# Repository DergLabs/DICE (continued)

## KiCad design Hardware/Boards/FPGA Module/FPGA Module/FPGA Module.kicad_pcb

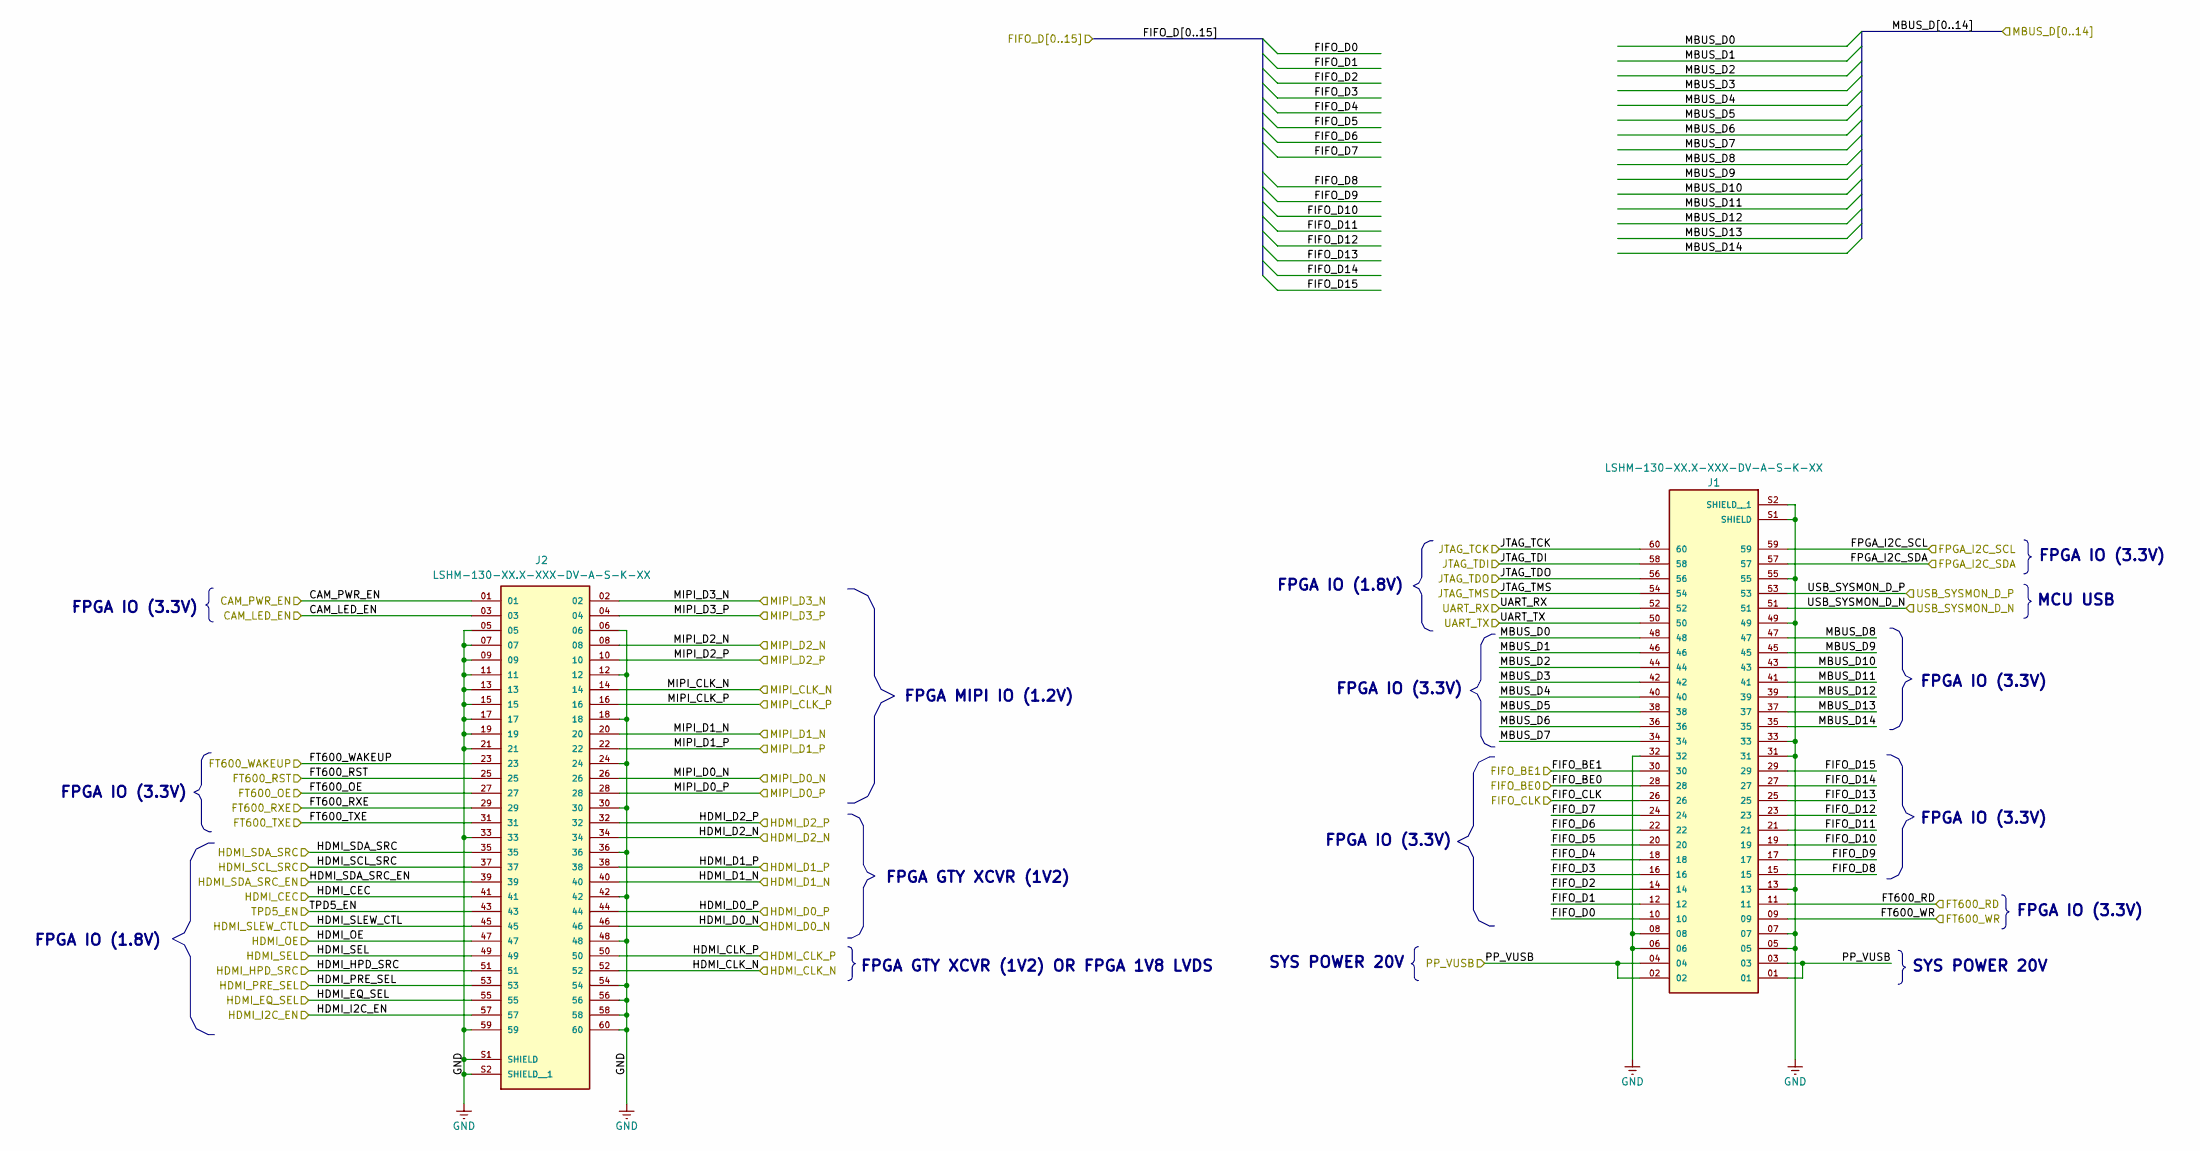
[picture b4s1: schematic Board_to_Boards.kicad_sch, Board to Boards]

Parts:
J1, J2: LSHM-130-XX.X-XXX-DV-A-S-K-XX; SAMTEC_LSHM-130-XX.X-XXX-DV-A-S-K-XX; PARTREV G

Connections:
/Top/Board to Boards/CAM_LED_EN: J2.03; also elsewhere on the board
/Top/Board to Boards/CAM_PWR_EN: J2.01; also elsewhere on the board
/Top/Board to Boards/FIFO_BE0: J1.28; also elsewhere on the board
/Top/Board to Boards/FIFO_BE1: J1.30; also elsewhere on the board
/Top/Board to Boards/FIFO_CLK: J1.26; also elsewhere on the board
/Top/Board to Boards/FIFO_D0: J1.10; also elsewhere on the board
/Top/Board to Boards/FIFO_D1: J1.12; also elsewhere on the board
/Top/Board to Boards/FIFO_D2: J1.14; also elsewhere on the board
/Top/Board to Boards/FIFO_D3: J1.16; also elsewhere on the board
/Top/Board to Boards/FIFO_D4: J1.18; also elsewhere on the board
/Top/Board to Boards/FIFO_D5: J1.20; also elsewhere on the board
/Top/Board to Boards/FIFO_D6: J1.22; also elsewhere on the board
/Top/Board to Boards/FIFO_D7: J1.24; also elsewhere on the board
/Top/Board to Boards/FIFO_D8: J1.15; also elsewhere on the board
/Top/Board to Boards/FIFO_D9: J1.17; also elsewhere on the board
/Top/Board to Boards/FIFO_D10: J1.19; also elsewhere on the board
/Top/Board to Boards/FIFO_D11: J1.21; also elsewhere on the board
/Top/Board to Boards/FIFO_D12: J1.23; also elsewhere on the board
/Top/Board to Boards/FIFO_D13: J1.25; also elsewhere on the board
/Top/Board to Boards/FIFO_D14: J1.27; also elsewhere on the board
/Top/Board to Boards/FIFO_D15: J1.29; also elsewhere on the board
/Top/Board to Boards/FPGA_I2C_SCL: J1.59; also elsewhere on the board
/Top/Board to Boards/FPGA_I2C_SDA: J1.57; also elsewhere on the board
/Top/Board to Boards/FT600_OE: J2.27; also elsewhere on the board
/Top/Board to Boards/FT600_RD: J1.11; also elsewhere on the board
/Top/Board to Boards/FT600_RST: J2.25; also elsewhere on the board
/Top/Board to Boards/FT600_RXE: J2.29; also elsewhere on the board
/Top/Board to Boards/FT600_TXE: J2.31; also elsewhere on the board
/Top/Board to Boards/FT600_WAKEUP: J2.23; also elsewhere on the board
/Top/Board to Boards/FT600_WR: J1.09; also elsewhere on the board
/Top/Board to Boards/HDMI_CEC: J2.41; also elsewhere on the board
/Top/Board to Boards/HDMI_CLK_N: J2.52; also elsewhere on the board
/Top/Board to Boards/HDMI_CLK_P: J2.50; also elsewhere on the board
/Top/Board to Boards/HDMI_D0_N: J2.46; also elsewhere on the board
/Top/Board to Boards/HDMI_D0_P: J2.44; also elsewhere on the board
/Top/Board to Boards/HDMI_D1_N: J2.40; also elsewhere on the board
/Top/Board to Boards/HDMI_D1_P: J2.38; also elsewhere on the board
/Top/Board to Boards/HDMI_D2_N: J2.34; also elsewhere on the board
/Top/Board to Boards/HDMI_D2_P: J2.32; also elsewhere on the board
/Top/Board to Boards/HDMI_EQ_SEL: J2.55; also elsewhere on the board
/Top/Board to Boards/HDMI_HPD_SRC: J2.51; also elsewhere on the board
/Top/Board to Boards/HDMI_I2C_EN: J2.57; also elsewhere on the board
/Top/Board to Boards/HDMI_OE: J2.47; also elsewhere on the board
/Top/Board to Boards/HDMI_PRE_SEL: J2.53; also elsewhere on the board
/Top/Board to Boards/HDMI_SCL_SRC: J2.37; also elsewhere on the board
/Top/Board to Boards/HDMI_SDA_SRC: J2.35; also elsewhere on the board
/Top/Board to Boards/HDMI_SDA_SRC_EN: J2.39; also elsewhere on the board
/Top/Board to Boards/HDMI_SEL: J2.49; also elsewhere on the board
/Top/Board to Boards/HDMI_SLEW_CTL: J2.45; also elsewhere on the board
/Top/Board to Boards/JTAG_TCK: J1.60; also elsewhere on the board
/Top/Board to Boards/JTAG_TDI: J1.58; also elsewhere on the board
/Top/Board to Boards/JTAG_TDO: J1.56; also elsewhere on the board
/Top/Board to Boards/JTAG_TMS: J1.54; also elsewhere on the board
/Top/Board to Boards/MBUS_D0: J1.48; also elsewhere on the board
/Top/Board to Boards/MBUS_D1: J1.46; also elsewhere on the board
/Top/Board to Boards/MBUS_D2: J1.44; also elsewhere on the board
/Top/Board to Boards/MBUS_D3: J1.42; also elsewhere on the board
/Top/Board to Boards/MBUS_D4: J1.40; also elsewhere on the board
/Top/Board to Boards/MBUS_D5: J1.38; also elsewhere on the board
/Top/Board to Boards/MBUS_D6: J1.36; also elsewhere on the board
/Top/Board to Boards/MBUS_D7: J1.34; also elsewhere on the board
/Top/Board to Boards/MBUS_D8: J1.47; also elsewhere on the board
/Top/Board to Boards/MBUS_D9: J1.45; also elsewhere on the board
/Top/Board to Boards/MBUS_D10: J1.43; also elsewhere on the board
/Top/Board to Boards/MBUS_D11: J1.41; also elsewhere on the board
/Top/Board to Boards/MBUS_D12: J1.39; also elsewhere on the board
/Top/Board to Boards/MBUS_D13: J1.37; also elsewhere on the board
/Top/Board to Boards/MBUS_D14: J1.35; also elsewhere on the board
/Top/Board to Boards/MIPI_CLK_N: J2.14; also elsewhere on the board
/Top/Board to Boards/MIPI_CLK_P: J2.16; also elsewhere on the board
/Top/Board to Boards/MIPI_D0_N: J2.26; also elsewhere on the board
/Top/Board to Boards/MIPI_D0_P: J2.28; also elsewhere on the board
/Top/Board to Boards/MIPI_D1_N: J2.20; also elsewhere on the board
/Top/Board to Boards/MIPI_D1_P: J2.22; also elsewhere on the board
/Top/Board to Boards/MIPI_D2_N: J2.08; also elsewhere on the board
/Top/Board to Boards/MIPI_D2_P: J2.10; also elsewhere on the board
/Top/Board to Boards/MIPI_D3_N: J2.02; also elsewhere on the board
/Top/Board to Boards/MIPI_D3_P: J2.04; also elsewhere on the board
/Top/Board to Boards/PP_VUSB: J1.01, J1.02, J1.03, J1.04; also elsewhere on the board
/Top/Board to Boards/TPD5_EN: J2.43; also elsewhere on the board
/Top/Board to Boards/UART_RX: J1.52; also elsewhere on the board
/Top/Board to Boards/UART_TX: J1.50; also elsewhere on the board
/Top/Board to Boards/USB_SYSMON_D_N: J1.51; also elsewhere on the board
/Top/Board to Boards/USB_SYSMON_D_P: J1.53; also elsewhere on the board

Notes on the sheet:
FPGA IO (3.3V)
FPGA GTY XCVR (1V2) OR FPGA 1V8 LVDS
FPGA GTY XCVR (1V2)
SYS POWER 20V
FPGA MIPI IO (1.2V)
MCU USB
FPGA IO (1.8V)

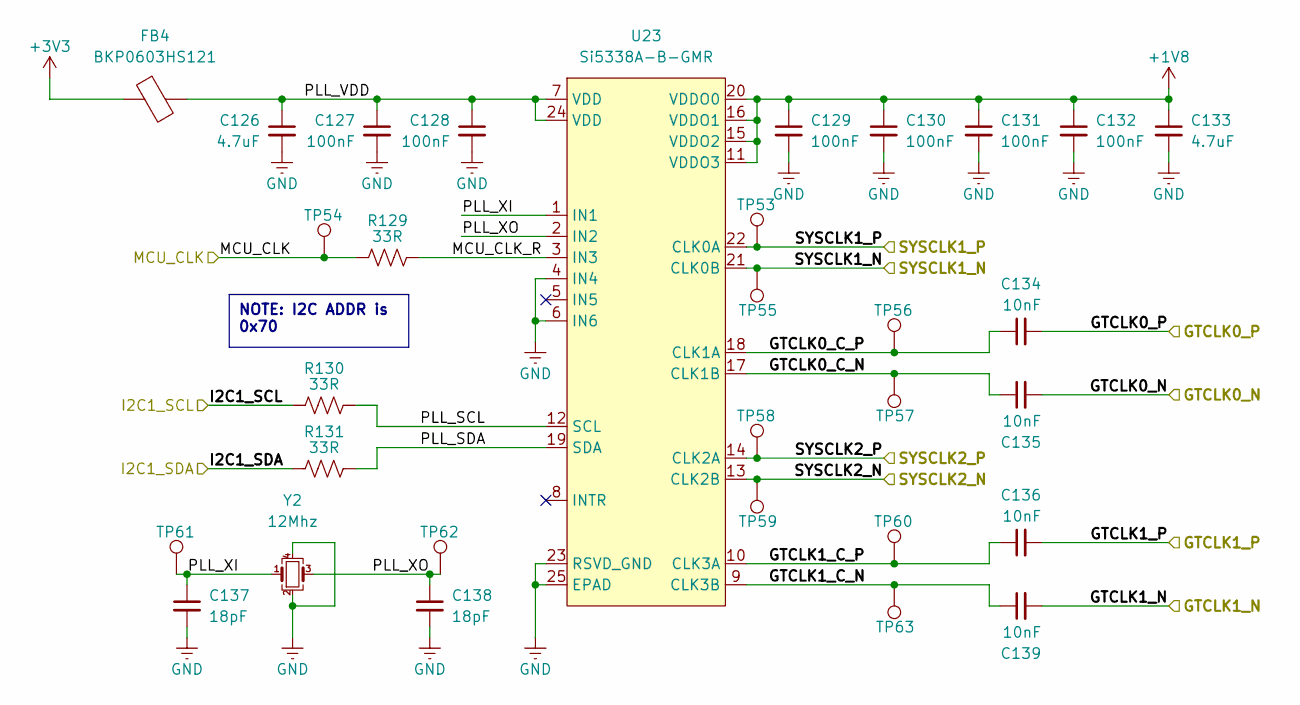
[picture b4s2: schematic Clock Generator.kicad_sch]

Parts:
C126, C133: 4.7uF; C_0402_1005Metric
C127, C128, C129, C130, C131, C132: 100nF; C_0201_0603Metric
C134, C135, C136, C139: 10nF; C_0201_0603Metric
C137, C138: 18pF; C_0201_0603Metric
FB4: BKP0603HS121; L_0201_0603Metric
R129, R130, R131: 33R; R_0201_0603Metric
TP53, TP54, TP55, TP56, TP57, TP58, TP59, TP60, TP61, TP62, TP63: Test Point; Test Point 0.75mm
U23: Si5338A-B-GMR; QFN-24-1EP_4x4mm_P0.5mm_EP2.6x2.6mm
Y2: 12Mhz; Oscillator_SMD_Abracon_ASE-4Pin_3.2x2.5mm

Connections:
+1V8: C129.1, C130.1, C131.1, C132.1, C133.1, U23.11 (VDDO3), U23.15 (VDDO2), U23.16 (VDDO1), U23.20 (VDDO0); also elsewhere on the board
/Top/Clock Generator/GTCLK0_C_N: C135.1, TP57.1, U23.17 (CLK1B)
/Top/Clock Generator/GTCLK0_C_P: C134.1, TP56.1, U23.18 (CLK1A)
/Top/Clock Generator/GTCLK0_N: C135.2; also elsewhere on the board
/Top/Clock Generator/GTCLK0_P: C134.2; also elsewhere on the board
/Top/Clock Generator/GTCLK1_C_N: C139.1, TP63.1, U23.9 (CLK3B)
/Top/Clock Generator/GTCLK1_C_P: C136.1, TP60.1, U23.10 (CLK3A)
/Top/Clock Generator/GTCLK1_N: C139.2; also elsewhere on the board
/Top/Clock Generator/GTCLK1_P: C136.2; also elsewhere on the board
/Top/Clock Generator/I2C1_SCL: R130.2; also elsewhere on the board
/Top/Clock Generator/I2C1_SDA: R131.2; also elsewhere on the board
/Top/Clock Generator/MCU_CLK: R129.2, TP54.1; also elsewhere on the board
/Top/Clock Generator/MCU_CLK_R: R129.1, U23.3 (IN3)
/Top/Clock Generator/PLL_SCL: R130.1, U23.12 (SCL)
/Top/Clock Generator/PLL_SDA: R131.1, U23.19 (SDA)
/Top/Clock Generator/PLL_VDD: C126.1, C127.1, C128.1, FB4.2, U23.7 (VDD), U23.24 (VDD)
/Top/Clock Generator/PLL_XI: C137.1, TP61.1, U23.1 (IN1), Y2.1
/Top/Clock Generator/PLL_XO: C138.1, TP62.1, U23.2 (IN2), Y2.3
/Top/Clock Generator/SYSCLK1_N: TP55.1, U23.21 (CLK0B); also elsewhere on the board
/Top/Clock Generator/SYSCLK1_P: TP53.1, U23.22 (CLK0A); also elsewhere on the board
/Top/Clock Generator/SYSCLK2_N: TP59.1, U23.13 (CLK2B); also elsewhere on the board
/Top/Clock Generator/SYSCLK2_P: TP58.1, U23.14 (CLK2A); also elsewhere on the board

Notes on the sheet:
NOTE: I2C ADDR is 0x70

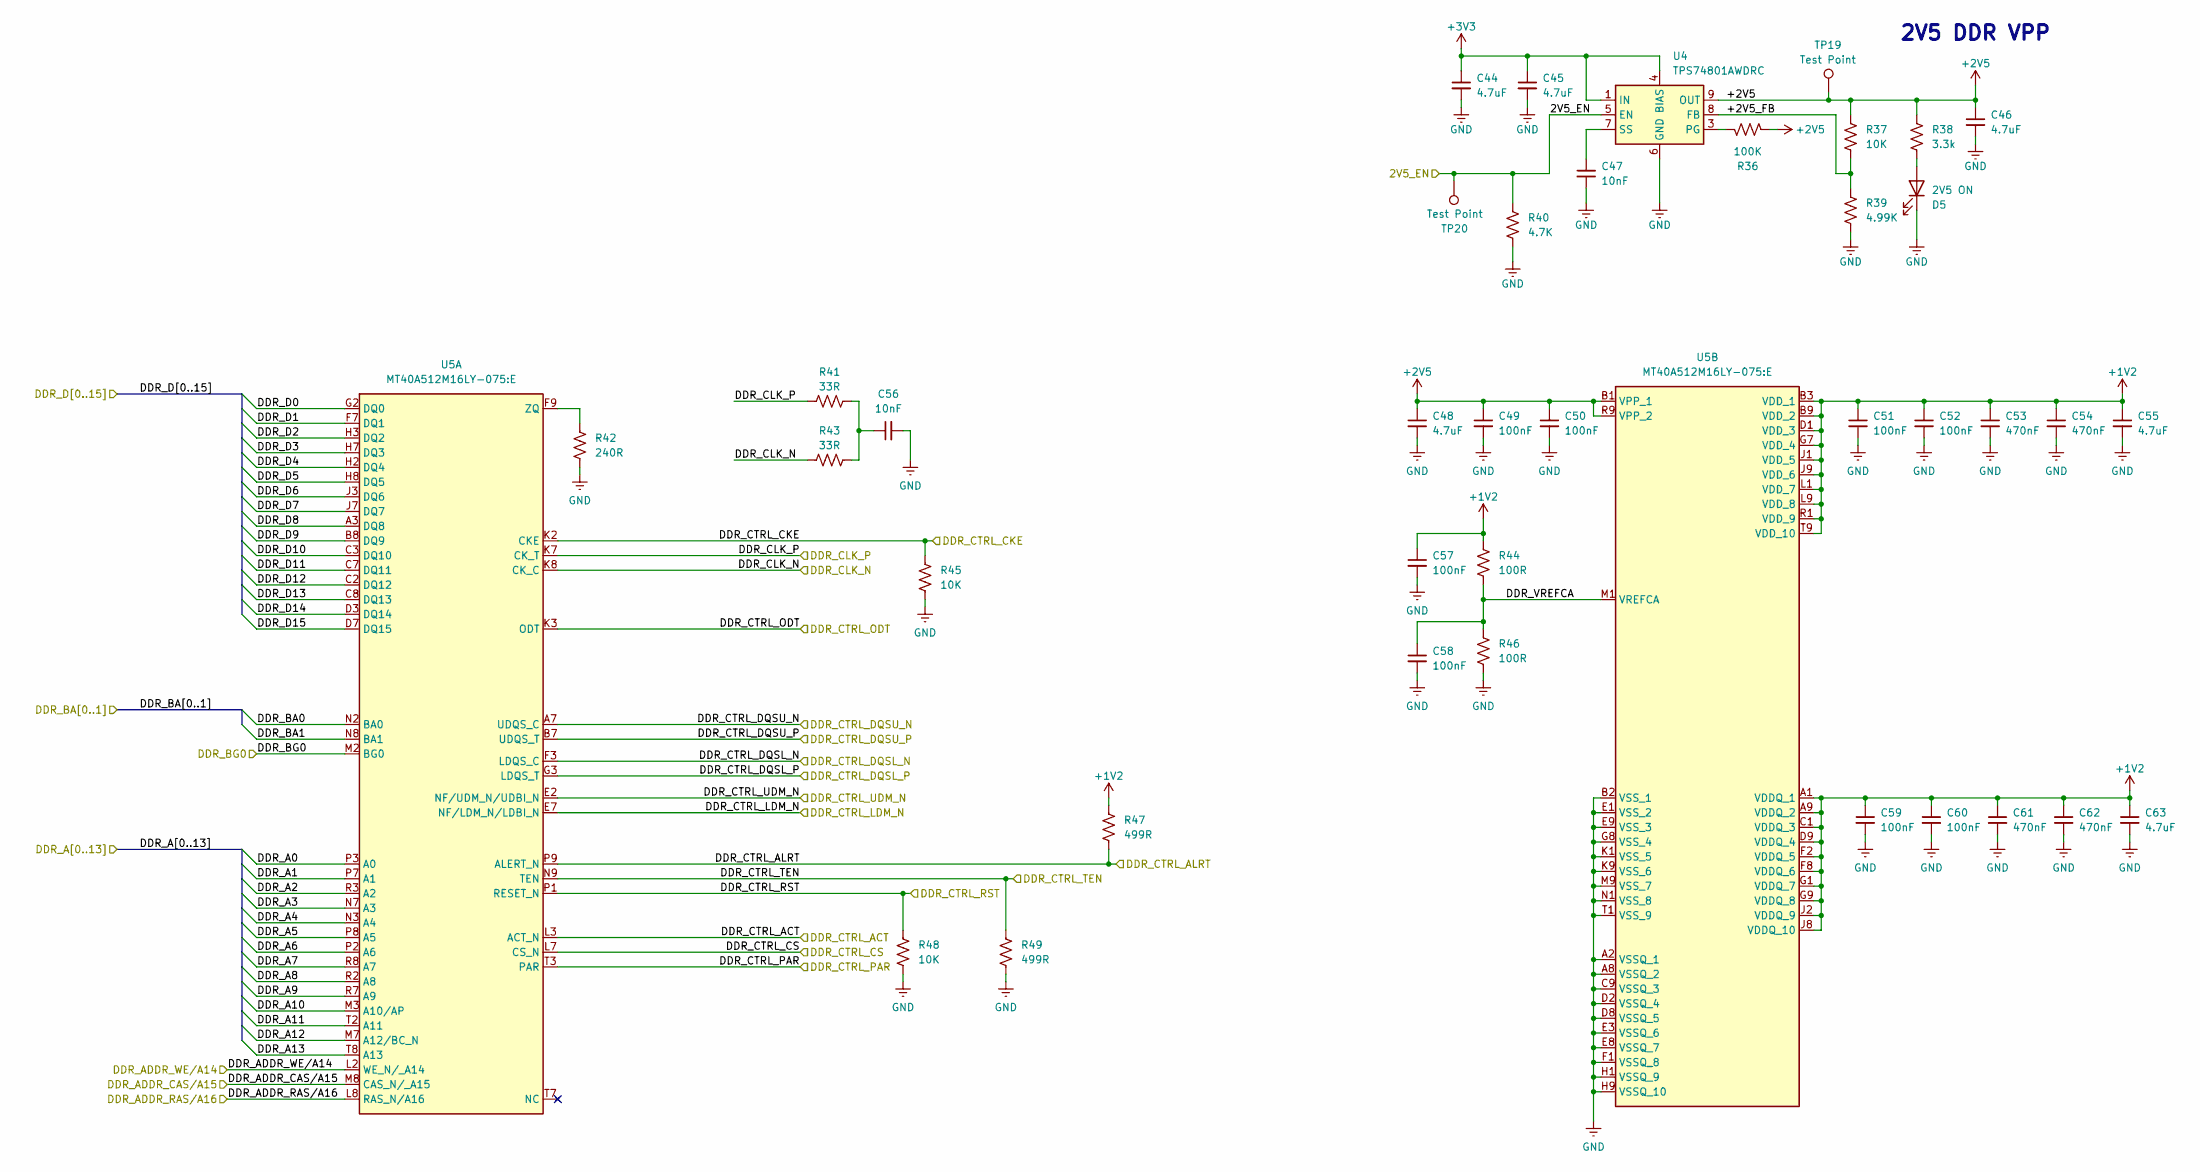
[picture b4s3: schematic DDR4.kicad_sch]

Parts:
C44, C45, C46, C48, C55, C63: 4.7uF; C_0402_1005Metric
C47, C56: 10nF; C_0201_0603Metric
C49, C50, C51, C52, C57, C58, C59, C60: 100nF; C_0201_0603Metric
C53, C54, C61, C62: 470nF; C_0201_0603Metric
D5: 2V5 ON; LED_0603_1608Metric
R36: 100K; R_0201_0603Metric
R37, R45, R48: 10K; R_0201_0603Metric
R38: 3.3k; R_0201_0603Metric
R39: 4.99K; R_0201_0603Metric
R40: 4.7K; R_0201_0603Metric
R41, R43: 33R; R_0201_0603Metric
R42: 240R; R_0201_0603Metric
R44, R46: 100R; R_0201_0603Metric
R47, R49: 499R; R_0201_0603Metric
TP19, TP20: Test Point; Test Point 0.75mm
U4: TPS74801AWDRC; VSON-10-1EP_3x3mm_P0.5mm_EP1.65x2.4mm_ThermalVias
U5: MT40A512M16LY-075:E; BGA96C80P9X16_750X1350X120

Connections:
+1V2: C51.1, C52.1, C53.1, C54.1, C55.1, C57.1, C59.1, C60.1, C61.1, C62.1, C63.1, R44.2, R47.2, U5.A1 (VDDQ_1), U5.A9 (VDDQ_2), U5.B3 (VDD_1), U5.B9 (VDD_2), U5.C1 (VDDQ_3), U5.D1 (VDD_3), U5.D9 (VDDQ_4), U5.F2 (VDDQ_5), U5.F8 (VDDQ_6), U5.G1 (VDDQ_7), U5.G7 (VDD_4), U5.G9 (VDDQ_8), U5.J1 (VDD_5), U5.J2 (VDDQ_9), U5.J8 (VDDQ_10), U5.J9 (VDD_6), U5.L1 (VDD_7), U5.L9 (VDD_8), U5.R1 (VDD_9), U5.T9 (VDD_10); also elsewhere on the board
+2V5: C46.1, C48.1, C49.1, C50.1, R36.2, R37.1, R38.1, TP19.1, U4.9 (OUT), U4.10 (OUT), U5.B1 (VPP_1), U5.R9 (VPP_2)
/Top/DDR4/2V5_EN: R40.2, TP20.1, U4.5 (EN); also elsewhere on the board
/Top/DDR4/+2V5_FB: R37.2, R39.1, U4.8 (FB)
/Top/DDR4/DDR_A0: U5.P3 (A0); also elsewhere on the board
/Top/DDR4/DDR_A1: U5.P7 (A1); also elsewhere on the board
/Top/DDR4/DDR_A2: U5.R3 (A2); also elsewhere on the board
/Top/DDR4/DDR_A3: U5.N7 (A3); also elsewhere on the board
/Top/DDR4/DDR_A4: U5.N3 (A4); also elsewhere on the board
/Top/DDR4/DDR_A5: U5.P8 (A5); also elsewhere on the board
/Top/DDR4/DDR_A6: U5.P2 (A6); also elsewhere on the board
/Top/DDR4/DDR_A7: U5.R8 (A7); also elsewhere on the board
/Top/DDR4/DDR_A8: U5.R2 (A8); also elsewhere on the board
/Top/DDR4/DDR_A9: U5.R7 (A9); also elsewhere on the board
/Top/DDR4/DDR_A10: U5.M3 (A10/AP); also elsewhere on the board
/Top/DDR4/DDR_A11: U5.T2 (A11); also elsewhere on the board
/Top/DDR4/DDR_A12: U5.M7 (A12/BC_N); also elsewhere on the board
/Top/DDR4/DDR_A13: U5.T8 (A13); also elsewhere on the board
/Top/DDR4/DDR_ADDR_CAS/A15: U5.M8 (CAS_N/_A15); also elsewhere on the board
/Top/DDR4/DDR_ADDR_RAS/A16: U5.L8 (RAS_N/A16); also elsewhere on the board
/Top/DDR4/DDR_ADDR_WE/A14: U5.L2 (WE_N/_A14); also elsewhere on the board
/Top/DDR4/DDR_BA0: U5.N2 (BA0); also elsewhere on the board
/Top/DDR4/DDR_BA1: U5.N8 (BA1); also elsewhere on the board
/Top/DDR4/DDR_BG0: U5.M2 (BG0); also elsewhere on the board
/Top/DDR4/DDR_CLK_N: R43.2, U5.K8 (CK_C); also elsewhere on the board
/Top/DDR4/DDR_CLK_P: R41.2, U5.K7 (CK_T); also elsewhere on the board
/Top/DDR4/DDR_CTRL_ACT: U5.L3 (ACT_N); also elsewhere on the board
/Top/DDR4/DDR_CTRL_ALRT: R47.1, U5.P9 (ALERT_N); also elsewhere on the board
/Top/DDR4/DDR_CTRL_CKE: R45.2, U5.K2 (CKE); also elsewhere on the board
/Top/DDR4/DDR_CTRL_CS: U5.L7 (CS_N); also elsewhere on the board
/Top/DDR4/DDR_CTRL_DQSL_N: U5.F3 (LDQS_C); also elsewhere on the board
/Top/DDR4/DDR_CTRL_DQSL_P: U5.G3 (LDQS_T); also elsewhere on the board
/Top/DDR4/DDR_CTRL_DQSU_N: U5.A7 (UDQS_C); also elsewhere on the board
/Top/DDR4/DDR_CTRL_DQSU_P: U5.B7 (UDQS_T); also elsewhere on the board
/Top/DDR4/DDR_CTRL_LDM_N: U5.E7 (NF/LDM_N/LDBI_N); also elsewhere on the board
/Top/DDR4/DDR_CTRL_ODT: U5.K3 (ODT); also elsewhere on the board
/Top/DDR4/DDR_CTRL_PAR: U5.T3 (PAR); also elsewhere on the board
/Top/DDR4/DDR_CTRL_RST: R48.2, U5.P1 (RESET_N); also elsewhere on the board
/Top/DDR4/DDR_CTRL_TEN: R49.2, U5.N9 (TEN); also elsewhere on the board
/Top/DDR4/DDR_CTRL_UDM_N: U5.E2 (NF/UDM_N/UDBI_N); also elsewhere on the board
/Top/DDR4/DDR_D0: U5.G2 (DQ0); also elsewhere on the board
/Top/DDR4/DDR_D1: U5.F7 (DQ1); also elsewhere on the board
/Top/DDR4/DDR_D2: U5.H3 (DQ2); also elsewhere on the board
/Top/DDR4/DDR_D3: U5.H7 (DQ3); also elsewhere on the board
/Top/DDR4/DDR_D4: U5.H2 (DQ4); also elsewhere on the board
/Top/DDR4/DDR_D5: U5.H8 (DQ5); also elsewhere on the board
/Top/DDR4/DDR_D6: U5.J3 (DQ6); also elsewhere on the board
/Top/DDR4/DDR_D7: U5.J7 (DQ7); also elsewhere on the board
/Top/DDR4/DDR_D8: U5.A3 (DQ8); also elsewhere on the board
/Top/DDR4/DDR_D9: U5.B8 (DQ9); also elsewhere on the board
/Top/DDR4/DDR_D10: U5.C3 (DQ10); also elsewhere on the board
/Top/DDR4/DDR_D11: U5.C7 (DQ11); also elsewhere on the board
/Top/DDR4/DDR_D12: U5.C2 (DQ12); also elsewhere on the board
/Top/DDR4/DDR_D13: U5.C8 (DQ13); also elsewhere on the board
/Top/DDR4/DDR_D14: U5.D3 (DQ14); also elsewhere on the board
/Top/DDR4/DDR_D15: U5.D7 (DQ15); also elsewhere on the board
/Top/DDR4/DDR_VREFCA: C58.1, R44.1, R46.2, U5.M1 (VREFCA)
unnamed: C56.1, R41.1, R43.1
unnamed: R36.1, U4.3 (PG)
unnamed: C47.1, U4.7 (SS)
unnamed: R42.2, U5.F9 (ZQ)

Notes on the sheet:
2V5 DDR VPP

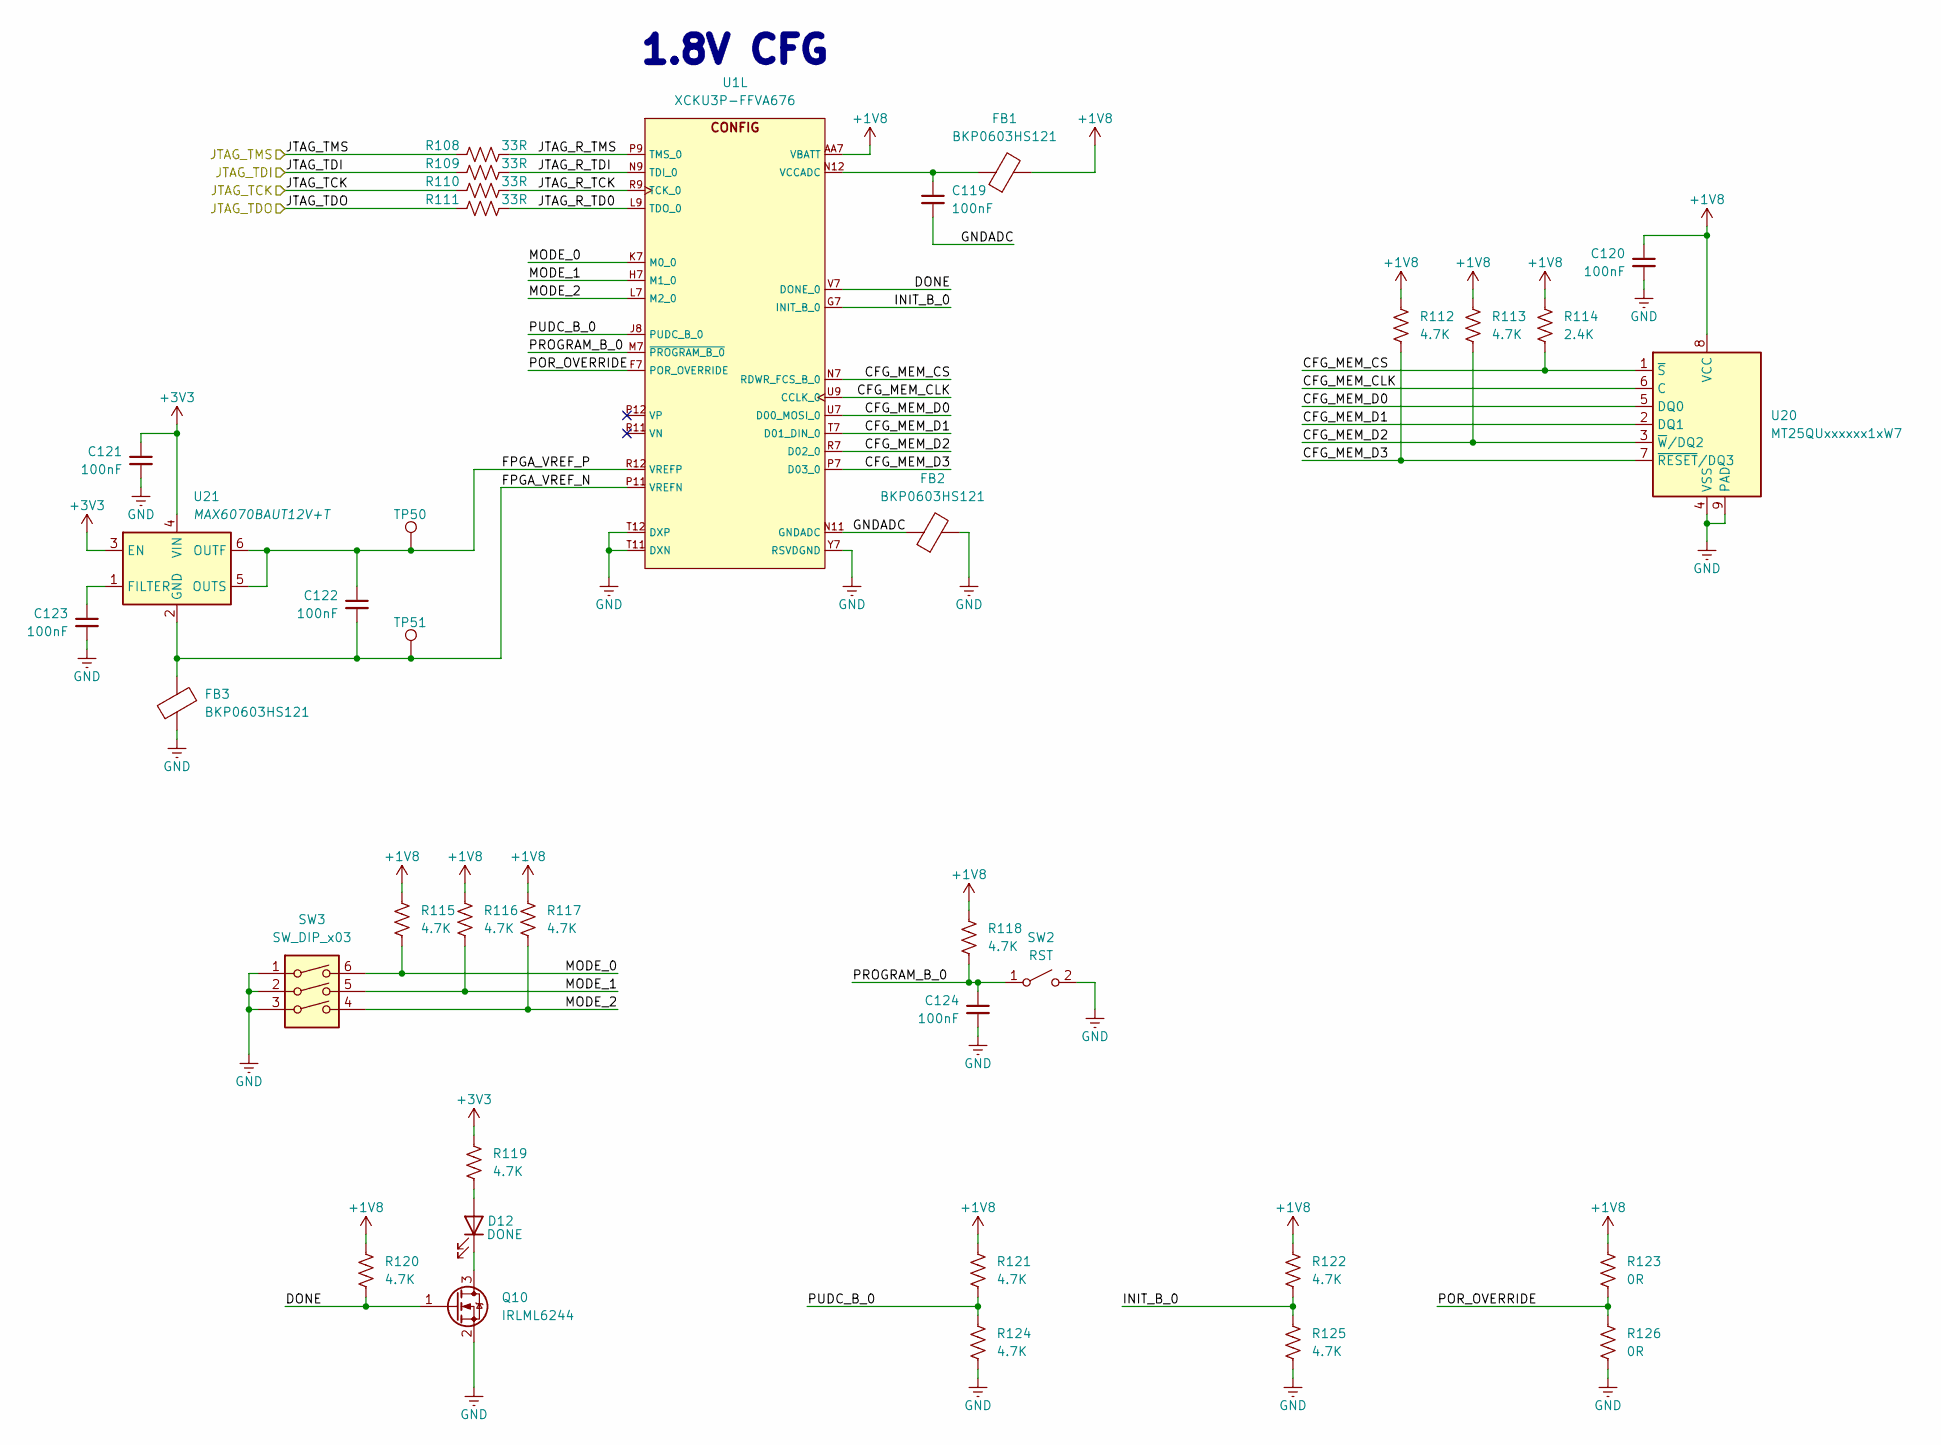
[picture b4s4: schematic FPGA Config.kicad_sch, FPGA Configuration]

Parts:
C119, C120, C121, C122, C123, C124: 100nF; C_0201_0603Metric
D12: DONE; LED_0603_1608Metric
FB1, FB2, FB3: BKP0603HS121; L_0201_0603Metric
Q10: IRLML6244; SOT-23
R108, R109, R110, R111: 33R; R_0201_0603Metric
R112, R113, R115, R116, R117, R118, R119, R120, R121, R122, R124, R125: 4.7K; R_0201_0603Metric
R114: 2.4K; R_0201_0603Metric
R123, R126: 0R; R_0201_0603Metric
SW2: RST; SW_Push_SPST_NO_Alps_SKRK
SW3: SW_DIP_x03; SW_DIP_SPSTx03_Slide_KingTek_DSHP03TJ_W5.25mm_P1.27mm_JPin; MPN 416131160803
TP50, TP51: Test Point; Test Point 0.75mm
U1: XCKU3P-FFVA676; BGA676
U20: MT25QUxxxxxx1xW7; W-PDFN-8-1EP_6x5mm_P1.27mm_EP3x3mm
U21: MAX6070BAUT12V+T; SOT-23-6

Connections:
+1V8: C120.1, FB1.2, R112.2, R113.2, R114.2, R115.2, R116.2, R117.2, R118.2, R120.2, R121.2, R122.2, R123.2, U1.AA7 (VBATT), U20.8 (VCC); also elsewhere on the board
/Top/Board to Boards/JTAG_TCK: R110.2; also elsewhere on the board
/Top/Board to Boards/JTAG_TDI: R109.2; also elsewhere on the board
/Top/Board to Boards/JTAG_TDO: R111.2; also elsewhere on the board
/Top/Board to Boards/JTAG_TMS: R108.2; also elsewhere on the board
/Top/FPGA Config/CFG_MEM_CLK: U1.U9 (CCLK_0), U20.6 (C)
/Top/FPGA Config/CFG_MEM_CS: R114.1, U1.N7 (RDWR_FCS_B_0), U20.1 (~S)
/Top/FPGA Config/CFG_MEM_D0: U1.U7 (D00_MOSI_0), U20.5 (DQ0)
/Top/FPGA Config/CFG_MEM_D1: U1.T7 (D01_DIN_0), U20.2 (DQ1)
/Top/FPGA Config/CFG_MEM_D2: R113.1, U1.R7 (D02_0), U20.3 (~W/DQ2)
/Top/FPGA Config/CFG_MEM_D3: R112.1, U1.P7 (D03_0), U20.7 (~RESET/DQ3)
/Top/FPGA Config/DONE: Q10.1 (G), R120.1, U1.V7 (DONE_0)
/Top/FPGA Config/FPGA_VREF_N: C122.2, FB3.1, TP51.1, U1.P11 (VREFN), U21.2 (GND)
/Top/FPGA Config/FPGA_VREF_P: C122.1, TP50.1, U1.R12 (VREFP), U21.5 (OUTS), U21.6 (OUTF)
/Top/FPGA Config/GNDADC: C119.2, FB2.1, U1.N11 (GNDADC)
/Top/FPGA Config/INIT_B_0: R122.1, R125.2, U1.G7 (INIT_B_0)
/Top/FPGA Config/JTAG_R_TCK: R110.1, U1.R9 (TCK_0)
/Top/FPGA Config/JTAG_R_TD0: R111.1, U1.L9 (TDO_0)
/Top/FPGA Config/JTAG_R_TDI: R109.1, U1.N9 (TDI_0)
/Top/FPGA Config/JTAG_R_TMS: R108.1, U1.P9 (TMS_0)
/Top/FPGA Config/MODE_0: R115.1, SW3.6, U1.K7 (M0_0)
/Top/FPGA Config/MODE_1: R116.1, SW3.5, U1.H7 (M1_0)
/Top/FPGA Config/MODE_2: R117.1, SW3.4, U1.L7 (M2_0)
/Top/FPGA Config/POR_OVERRIDE: R123.1, R126.2, U1.F7 (POR_OVERRIDE)
/Top/FPGA Config/PROGRAM_B_0: C124.1, R118.1, SW2.1 (A), U1.M7 (~PROGRAM_B_0)
/Top/FPGA Config/PUDC_B_0: R121.1, R124.2, U1.J8 (PUDC_B_0)
unnamed: D12.2 (A), R119.1
unnamed: D12.1 (K), Q10.3 (D)
unnamed: C119.1, FB1.1, U1.N12 (VCCADC)
unnamed: C123.1, U21.1 (FILTER)

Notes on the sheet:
1.8V CFG
